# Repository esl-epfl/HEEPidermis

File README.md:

# Welcome!

HEEPidermis is a chip based on the open-source RISC-V platform [X-HEEP](https://github.com/esl-epfl/x-heep) intended to record Galvanic Skin Response (GSR) and Impedance (Z).
HEEPidermis is capable of injecting arbitrary-wave currents on the skin with an 8-bit iDAC and measure voltage through a 14-bit VCO-based ADC.
Parameters of the iDAC and ADC can be programmed dynamically using the on-board Ibex CPU. Acquired data can be stored in the 16 kB RAM memory for on-chip processing, compression, and transmission.

HEEPidermis can be interfaced through JTAG for code-debugging, SPI to obtain recordings from memory, or UART.
External ADCs and peripherals can also be commanded via SPI.

The Direct Memory Access (DMA) block allows the chip to operate autonomously without the constant interaction of the CPU. Given proper configuration, the DMA can take care of controlling the current injection profile, read data from the local ADC (or an external one), store data and/or transmit it through SPI.
The DMA can additionally re-direct data to a digital Level Crossing (dLC) block to filter data and reduce the output data rate. The output of the dLC can be stored in memory (along timestamps) or be exposed to be used as feedback loop for the analog front-end, interface with transmission circuits or as input to Spiking Neural Networks.
The dLC block also accepts inputs from analog LC ADCs (instead of the on-chip ADC).

HEEPidermis can also decimate 1-bit ΔΣ-ADCs' output with an integrated CIC filter or, alternatively, with an integrated custom smoothing stage, followed by the dLC block.

Being based on the X-HEEP platform, you can check its documentation on how to program, debug, or understand how it was built. We suggest using the [vendorized X-HEEP's documentation](../../hw/vendor/x-heep/docs/source/index.rst).
For all HEEPidermis-specific documentation, please refer to the documentation below.

<p align="center">

&nbsp;&nbsp;&nbsp;

</p>

## Index

- **Analog Front End**
  - [Analog subsystem](hw/ip/analog_subsystem/README.md)
  - [iDAC](hw/vendor/analog-library/iDAC/docs/README.md)
  - [VCO](hw/vendor/analog-library/VCO/docs/README.md)

- **Digital Back End**
  - [CPU](./docs/source/DBE/CPU.md)
  - [DMA (how we use it)](./docs/source/DBE/DMA.md)
  - [DMA](hw/vendor/x-heep/docs/source/Peripherals/DMA.md)
  - [SPI host](hw/vendor/x-heep/docs/source/Peripherals/SPI.md)
  - [SPI slave](hw/vendor/x-heep/docs/source/Peripherals/SPI_slave.md)
  - [digital Level-Crossing](hw/vendor/x-heep/docs/source/ExternalPeripherals/dLC.md)
  - [ΔΣ decimation (CIC filter)](./docs/source/DBE/CIC_filter.md)
  - [ΔΣ decimation (SES filter)](./docs/source/DBE/SES_filter.md)

- **PCBs**
  - [CHEEP-boards](./hw/vendor/cheep-boards/) - To program and provide power
  - [Breakout board](./hw/vendor/breakout-board/) - To solder the cheep and connect it to the CHEEP-boards.

- **Software**
  - [Desktop GUI](./sw/gui/README.md)

- **Related documents**
  - [HEEPidermis](https://arxiv.org/abs/2509.04528)
  - [ΔΣ Decimation theory](https://ieeexplore.ieee.org/abstract/document/11044062)
  - [iDAC precursor](https://ieeexplore.ieee.org/document/11044212)
  - [VCO Design](https://arxiv.org/abs/2509.06698)

## Desktop GUI

HEEPidermis includes a desktop GUI to configure the board, build firmware, record GSR signals, and visualize and analyze recordings. Adjust the injected current and sampling frequency live, explore saved recordings, and export your data to CSV.

Launch it from the repository root with:

```sh
make gui
```

See the [GUI documentation](./sw/gui/README.md) for installation requirements and usage instructions.

## Evaluating trade-offs in GSR recording

HEEPidermis is a complex SoC, and acquiring GSR keepeing a proper range, sensitivity, dynamic range, resolution and power can be very tricky! To aid in the process of choosing the right parameters we have modeled the performance and consumption of our front-end and integrated it into a visual model with which you can play.

You can use the plotter in two different ways:

1. **Forward control**: You choose the operating variables (injected current and sampling frequency) and study the obtained sensitivity for a given baseline value of conductivity (G)
2. **Target**: You select a target sensitivty and power consumption and let the tool find the optimal configuration.

To view the interactive plotter on your browser (forward mode only) run:
```
make plotter
```

## Making a GSR recording

We make GSR recordings by biasing the skin to the LDO's output at 0.8 V and using a second electrode to train current from the skin using the iDAC. The VCO measures that same node and the CPU computes the drop (knowing the LDO's output).

Because the computation is far from trivial we have added [a GSR SDK](./sw/external/lib/sdk/GSR) that takes care of managing peripherals and parameters to do the correct conversion to skin's conductance in nS. You can run the example application:

```
make app PROJECT=test_reconstruction BOOT_MODE=force
make verilator-run BOOT_MODE=force # Takes long, be patient :P (or cancel anytime with Ctrl+C and go ahead with the next step)
make verilator-waves
```

You will be able to see the input resistance (in Ω) and at the top (in yellow) the computed conductance (in nS). This simulation uses the behavioral models of the front-end, including an approximation of the VCO's measured phase noise.

## Prerequisites

Since this project is based on _X-HEEP_, it has the same prerequisites.

1. Follow _X-HEEP_'s [_Prerequisite_](https://github.com/esl-epfl/x-heep/tree/main#prerequisite) section to download the necessary tools.
To correctly generate hardware and software, an extended version of the _core-v-mini-mcu_ environment is required. To install it run:
   ```Bash
   make conda
   ```
Make sure the Conda environment is active:
   ```Bash
   conda activate heepidermis
   ```

2. Make sure that the following tools are available in your system's `PATH`:
   - To compile code: **RISC-V toolchain version 2022.01.17**, supporting at least `rv32imc`. Newer versions will work but compilation will have a bug when reporting memory usage.
   - To format SystemVerilog (in case you want to open a PR): **Verible version 0.0-4023-gc1271a00**
   - To simulate (open source): **Verilator 4.210**
   - To see waveforms out of Verilator: **GTKWave**
   - In case you have the licences:
     - Siemens QuestaSim version 2020.4 or above
     - Synopsys Design Compiler version 2020.09 or above

You can follow the instructions on how to install these tools on the [X-HEEP documentation - Manual setup](https://x-heep.readthedocs.io/en/latest/GettingStarted/Setup.html#manual-setup).

## Preparing the Boards

The easiest way to test HEEPidermis is to use the [CHEEP-boards](./hw/vendor/cheep-boards/), which provide all the tools (sw and hardware) to supply power and program HEEPidermis.

HEEPidermis is soldered (or placed on a socket) on the [breakout board](./hw/vendor/breakout-board/).

After soldering everything, you also need to:

### Connect chewing-gums

The chewing-gum (CG) boards are small shields that are connected to the main board, and which can be used to provide power or reference voltages to HEEPidermis, and measure that consumption.

| CG | Function | Nominal value | CG | Function | Nominal value |
| :--- | :--- | :--- | :--- | :--- | :--- |
| 6 | DCORE VDD | 0.8 V | 7 | ACORE VDD | 1.2 V |
| 5 | IO VDD | 1.8 V | 8 | iREF | Connect a source of 400 nA |
| 4 | not used | - | 9 | REF VDD | 1.2 V |
| 3 | not used | - | 10 | LDO VREF | 0.8 V |
| 2 | not used | - | 11 | VCO VDD | 0.8 V |
| 1 | not used | - | 12 | LDO VDD | 1.2 V |

> _Note that the bottom three CGs on the picture below are not used, they are just used to inject voltages here and there with an external cable for testing._

⚠️ Remember to solder a shunt resistor below the CG! ~10 Ω should do fine for the range 1-100 µW. Consider that the INA will amplify the drop by 1000-2000×, has an offset of some 10s µV, and it cannot output more than 3.3 V.

### Connect jumpers and switches

On the main board
* Each CG has three jumpers. To control them with the trimmer, connect the jumper next to it towards its screw. Connect the jumper on the side away from the trimmer to turn the power on. Connect the jumper innermost to the main baord away from the test point to make the output go to the main board.
* Connect the jumper for the IO VDD (next to CG 8) on 1.8 V
* No need to connect any jumper next to the oscilaltor (bottom of the main board)

On the breakout board there are several places where to connect jumpers to use the cheep on different configurations. Mainly, there are two rulers of pin headers around the cheep which can be used to connect or disconnect supplies. Many of them are short-circuited on both sides, so you just use the headers as test points or to inject a signal. The rest are marked with what would get to the cheep if you close the jumper. Additionally there are three-pin jumpers for you to choose what to supply the cheep with: an ideal supply coming from the main board's chewing gums, or a voltage/current coming from the on-cheep supplies.

Check the table on [the breakout board's readme](./hw/vendor/cheep-boards/) to see what connects what.

> ❗There are two pads on the bottom of the board that need to be short-circuited: They will connect the clock input to the cheep. You can select where to take the clock, if you have no clue what to do, put some solder tin on the two pair of pads that point to the main board to take the clock from there. Don't worry if you make a mistake and short a bit the other, it's not the end of the world.

There is a pair of switches on the breakout board, to the left of the cheep. You can eiter solder the switches to select the boot mode, or you can short with tin them the mid-pin with the one closest to the cheep to only use JTAG mode (explained below).

### Bug correction

🪲 You need to cut the pin below the `value` pin (the outter most pin, in row 31 of the main board) in the connector to the main board or nothing will work, sorry.

## Programming the ASIC

You can program the ASIC through 3 alternatives:
 - JTAG
 - Loading an external flash that HEEPidermis can read through SPI
 - Loading the program in RAM through the SPI slave peripheral

### Programming through JTAG

You need to connect the JTAG interface to an FTDI chip. This is avaialble on the [EPFL programmer](https://github.com/esl-epfl/x-heep-programmer-pmod) or on the [CHEEP boards](https://eslgit.epfl.ch/heep/cheep-boards) (currently only available upon request).

1. The BOOT switches should be set to

| Signal     | Value |
|------------|-------|
| FLASH_EXEC | 0     |
| BOOT_SEL   | 0     |

2. Set the system clock to 1 MHz. You can do that in two steps if you have the CHEEP board, and have exported the variable `$CHEEP_BOARDS` pointing to the folder where the repo is.
```bash
make board_config
make board_freq PLL_FREQ=1_000_000  #default
```

3. Build the SW/HW stack of the cheep
```bash
make cheep-gen
```

4. Compile the code
```bash
make app BOOT_MODE=jtag
```

1. Open openOCD and picocom to see the UART output
```bash
make jtag_open
```
1. Open GDB and run the program
```bash
make jtag_run
```
Useful commands:
> `c` (continue)
>
> `monitor reset hart`
>
> `monitor pc _start`
>
> `si` (next instruction)
>
> `disassembler`
>
> `x/8i` (see the following instructions).

1. Exit GDB with `ctrl+C` and type `quit`
2. Close the openOCD and uart terminals with
```bash
make jtag_close
```

### Programming from the FLASH

Testing... we seem to have a bug on the main board that prevents this from working 😬

### Programming through SPI

Testing...

## RTL Simulation

The included [`makefile`](./makefile) proves all the necessary rules to build _HEEPidermis_:

1. Generate all the RTL files (and software headers):
   ```bash
   make cheep-gen
   ```
   Some _X-HEEP_ configuration parameters (e.g. `BUS`, `MEMORY_BANKS` etc.) are still supported, although the default configuration may differ (check [`peripherals_config`](./config/peripherals_config)). In general, these should not be passed through the makefile targets but should be configured in the hjson files in the `config` folder.

2. Build the simulation model:
   ```bash
   make verilator-build     # Verilator
   make questasim-build     # QuestaSim
   ```

3. The software build process is primarily handled by _X-HEEP_, and most of its [example applications](./hw/vendor/x-heep/sw/applications/) will work on _HEEPidermis_ as well. You can choose other `BOOT_MODE`, just be sure to match it with the one used with `make *-build` (by default they use `fore`). `force` will be the faster for simulation.

```bash
make app PROJECT=test_dlc_vco BOOT_MODE=force
```

The combinations of compatible linker and boot modes can be found here:

1. Launch the simulation with the compiled firmware:
   ```bash
   make verilator-run       # Verilator with waveforms dump
   make verilator-opt       # Verilator without waveforms dump
   make questasim-run       # QuestaSim
   make questasim-gui       # QuestaSim with GUI
   ```

   You can also set other parameters like the `FUSESOC_FLAGS`, `LOG_LEVEL`, `BOOT_MODE`, `VCD_MODE`, etc. to customize the simulation. Refer to the [`makefile`](./makefile) for more details.

2. _HEEPidermis_ `stdout` is exposed through a UART DPI interface at `/dev/pts/<N>`, where `N` is a number printed on the simulation log during execution. You can connect to it using `screen` or similar tools, e.g.:
   ```bash
   screen /dev/pts/0
   ```
   The UART output is also stored to the `uart.log` file in the common simulation directory (`build/sim-common/uart.log`).
   > Using `printf()` will significantly increase the firmware execution time and therefore the simulation. For quick debugging, it recommended to use the return value from `main` instead. When it is _not_ zero, the testbench will print it out at the end of the simulation.

3. The waveforms dumped during the simulation can be opened using:
   ```bash
   make verilator-waves # after Verilator simulation
   make questasim-waves # after QuestaSim simulation
   ```

This will open the waveforms (example from `test_dlc_vco` application):

Assuming that your firmware is already available, steps 1., 3., and 4. can be repeated with a single command using the `verilator-sim` or `questasim-sim` targets.

# Questions?

Have questions? curiosities? ideas on how to exploit HEEPidermis? Want to contribute on following versions of the SoC?
Drop an email :) juan.sapriza@epfl.ch

# 📄 Reference

Want to know more details? Found HEEPidermis useful for your research? Cite our [LASCAS paper](https://ieeexplore.ieee.org/document/11457136).

```
@INPROCEEDINGS{11457136,
  author={Sapriza, Juan and Grassano, Beatrice and Naclerio, Alessio and Quadri, Filippo and Terzano, Tommaso and Mallasén, David and Schiavone, Davide and Leplae, Robin and Moullet, Jérémie and Levisse, Alexandre and Müller, Christoph and Graziano, Mariagrazia and Miguez, Matías and Atienza, David},
  booktitle={2026 IEEE 17th Latin America Symposium on Circuits and System (LASCAS)},
  title={HEEPidermis: A Versatile SoC for BioZ Recording},
  year={2026},
  pages={1-5},
  doi={10.1109/LASCAS67804.2026.11457136}}
```

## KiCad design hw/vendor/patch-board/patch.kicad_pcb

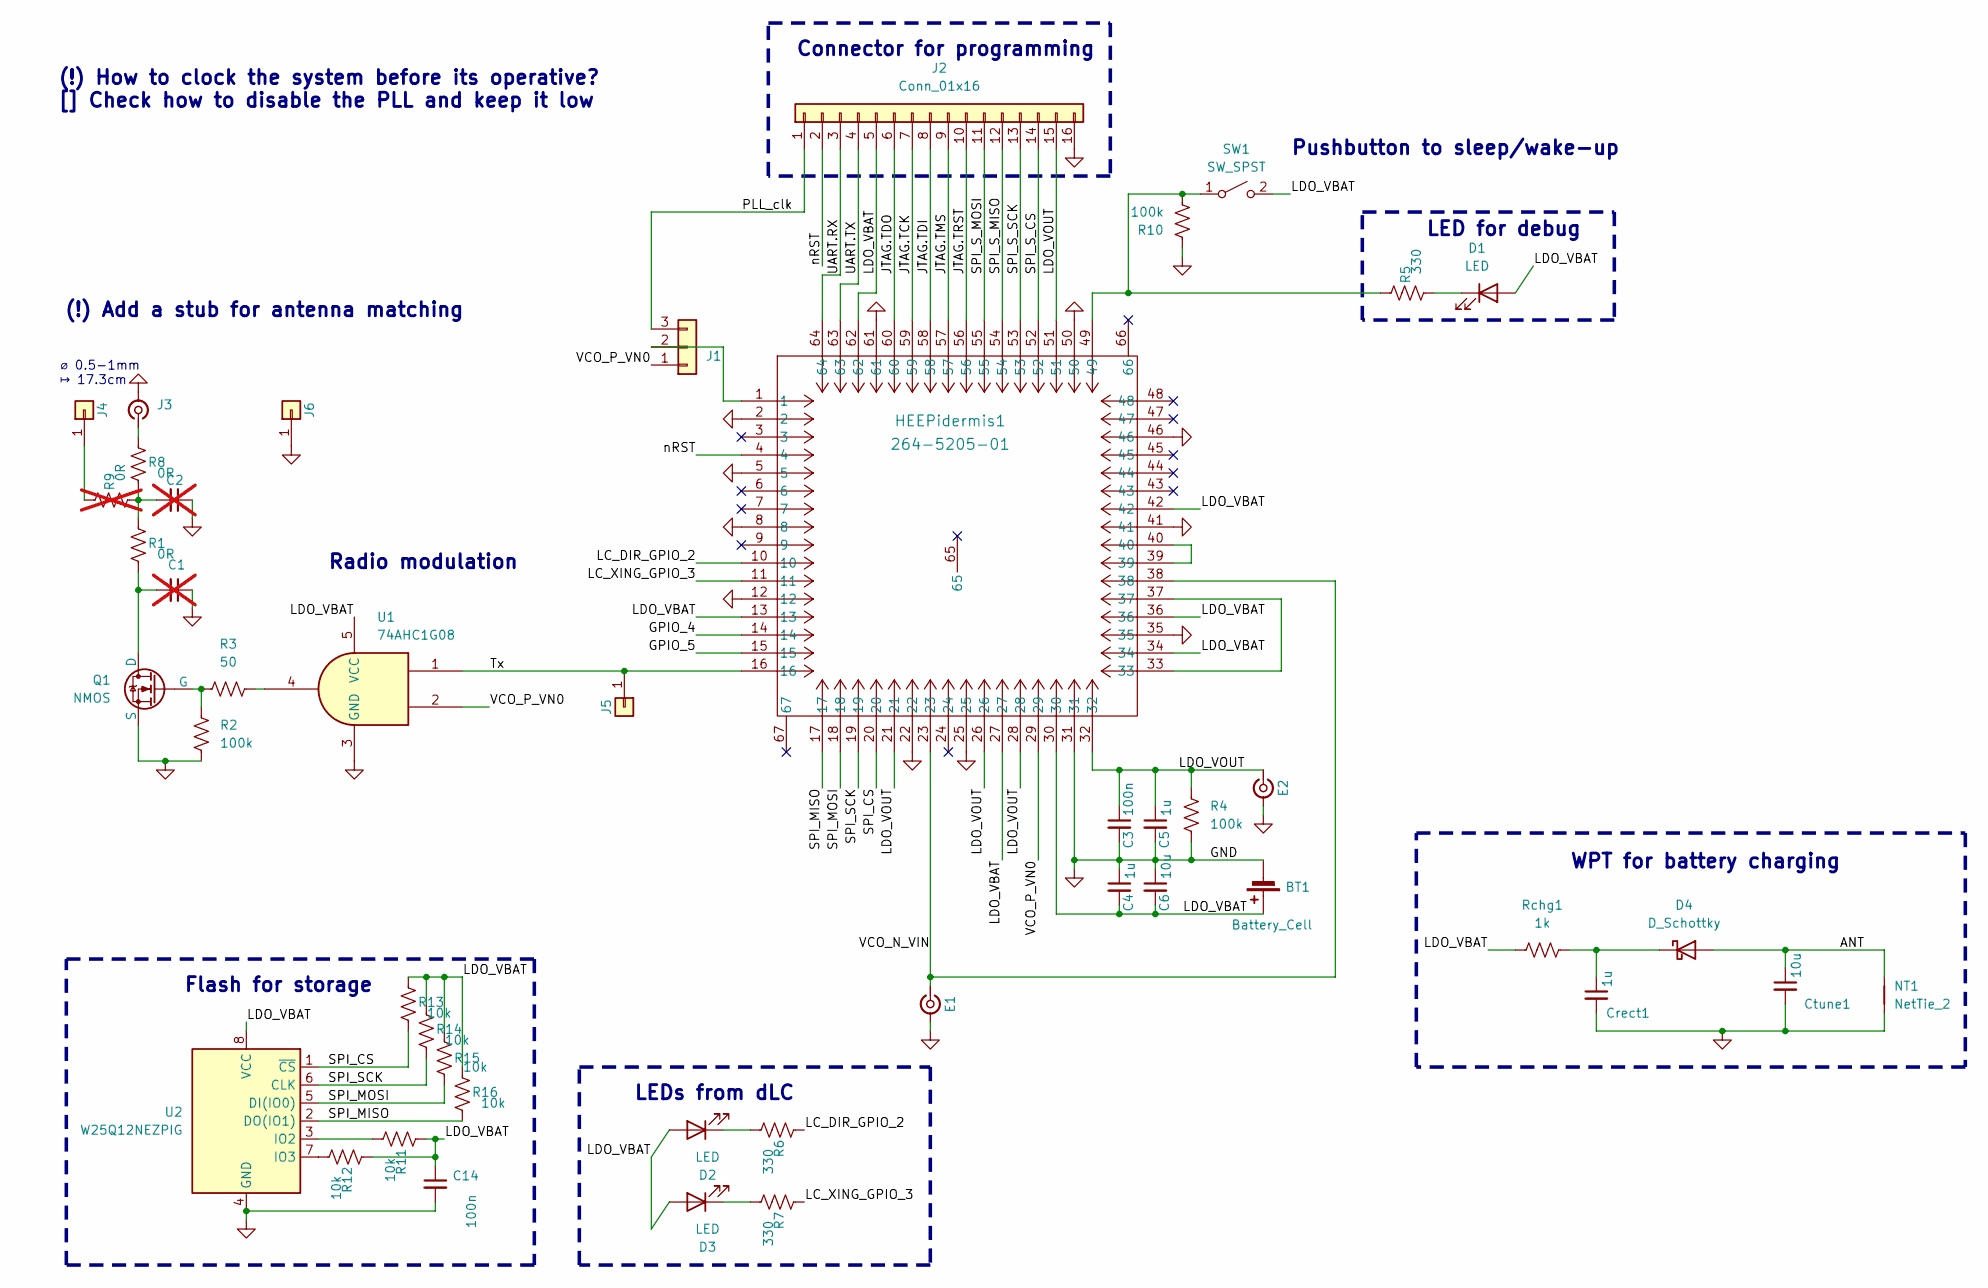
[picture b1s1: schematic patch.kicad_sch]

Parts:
BT1: Battery_Cell; BatteryHolder_Seiko_MS621F
C1, C2: C_0603_1608Metric; Mouser Part Number 80-C0805C104Z3V; Digikey Part Number 399-9158-1-ND; not fitted
C3, C14: 100n; C_0603_1608Metric; Mouser Part Number 80-C0805C104Z3V; Digikey Part Number 399-9158-1-ND
C4, C5: 1u; C_0603_1608Metric; Mouser Part Number 80-C0805C104Z3V; Digikey Part Number 399-9158-1-ND
C6: 10u; C_0603_1608Metric; Mouser Part Number 80-C0805C104Z3V; Digikey Part Number 399-9158-1-ND
Crect1: 1u; C_0603_1608Metric; Mouser Part Number 80-C0805C104Z3V; Digikey Part Number 399-9158-1-ND
Ctune1: 10u; C_0603_1608Metric; Mouser Part Number 80-C0805C104Z3V; Digikey Part Number 399-9158-1-ND
D1, D2, D3: LED; LED_0603_1608Metric
D4: D_Schottky; D_0603_1608Metric
E1, E2: Conn_Coaxial_Small; 4mm_snap_socket
HEEPidermis1: 264-5205-01; QFN-64-1EP_9x9mm_P0.5mm_EP3.4x3.4mm
J1: Conn_01x03; PinHeader_1x03_P1.00mm_Horizontal
J2: Conn_01x16; PinHeader_1x16_P1.00mm_Horizontal
J3: Conn_Coaxial_Small
J4, J5, J6: Conn_01x01; PinHeader_1x01_P2.54mm_Vertical
NT1: NetTie_2; 1MHz_coil_29x14
Q1: NMOS; SOT-323_SC-70_Handsoldering
R1, R8: 0R; R_0603_1608Metric
R2, R4, R10: 100k; R_0603_1608Metric
R3: 50; R_0603_1608Metric
R5, R6, R7: 330; R_0603_1608Metric
R9: 0R; R_0603_1608Metric; not fitted
R11, R12, R13, R14, R15, R16: 10k; R_0603_1608Metric
Rchg1: 1k; R_0603_1608Metric
SW1: SW_SPST; SPST_1.6x3mm
U1: 74AHC1G08; SOT-353_SC-70-5_Handsoldering
U2: W25Q12NEZPIG; SOIC-8_5.23x5.23mm_P1.27mm

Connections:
/ANT: Ctune1.1, D4.2 (A), NT1.2
/GPIO_4: HEEPidermis1.14
/GPIO_5: HEEPidermis1.15
/JTAG.TCK: HEEPidermis1.59, J2.7
/JTAG.TDI: HEEPidermis1.58, J2.8
/JTAG.TDO: HEEPidermis1.60, J2.6
/JTAG.TMS: HEEPidermis1.57, J2.9
/JTAG.TRST: HEEPidermis1.56, J2.10
/LC_DIR_GPIO_2: HEEPidermis1.10, R6.2
/LC_XING_GPIO_3: HEEPidermis1.11, R7.2
/LDO_VBAT: BT1.1 (+), C4.2, C6.2, C14.1, D1.2 (A), D2.2 (A), D3.2 (A), HEEPidermis1.13, HEEPidermis1.27, HEEPidermis1.30, HEEPidermis1.34, HEEPidermis1.36, HEEPidermis1.42, HEEPidermis1.62, J2.5, R11.2, R12.2, R13.2, R14.2, R15.2, R16.2, Rchg1.1, SW1.2 (B), U1.5 (VCC), U2.8 (VCC)
/LDO_VOUT: C3.1, C5.1, E2.1 (In_1), HEEPidermis1.21, HEEPidermis1.26, HEEPidermis1.28, HEEPidermis1.32, HEEPidermis1.51, J2.15, R4.1
/PLL_clk: J1.3, J2.1
/SPI_CS: HEEPidermis1.20, R13.1, U2.1 (~CS)
/SPI_MISO: HEEPidermis1.17, R16.1, U2.2 (DO(IO1))
/SPI_MOSI: HEEPidermis1.18, R15.1, U2.5 (DI(IO0))
/SPI_SCK: HEEPidermis1.19, R14.1, U2.6 (CLK)
/SPI_S_CS: HEEPidermis1.52, J2.14
/SPI_S_MISO: HEEPidermis1.54, J2.12
/SPI_S_MOSI: HEEPidermis1.55, J2.11
/SPI_S_SCK: HEEPidermis1.53, J2.13
/Tx: HEEPidermis1.16, J5.1 (Pin_1_1), U1.1
/UART.RX: HEEPidermis1.64, J2.3
/UART.TX: HEEPidermis1.63, J2.4
/VCO_N_VIN: E1.1 (In_1), HEEPidermis1.23, HEEPidermis1.38
/VCO_P_VN0: HEEPidermis1.29, J1.1, U1.2
/nRST: HEEPidermis1.4, J2.2
GND: BT1.2 (-), C1.1, C2.1, C3.2, C4.1, C5.2, C6.1, C14.2, Crect1.2, Ctune1.2, E1.2 (Ext), E2.2 (Ext), HEEPidermis1.2, HEEPidermis1.5, HEEPidermis1.8, HEEPidermis1.12, HEEPidermis1.22, HEEPidermis1.25, HEEPidermis1.31, HEEPidermis1.35, HEEPidermis1.41, HEEPidermis1.46, HEEPidermis1.50, HEEPidermis1.61, J2.16, J3.2 (Ext), J6.1 (Pin_1_1), NT1.1, Q1.3 (S), R2.1, R4.2, R10.2, U1.3 (GND), U2.4 (GND)
unnamed: C2.2, R1.2, R8.1, R9.1
unnamed: D1.1 (K), R5.1
unnamed: D2.1 (K), R6.1
unnamed: D3.1 (K), R7.1
unnamed: Crect1.1, D4.1 (K), Rchg1.2
unnamed: HEEPidermis1.33, HEEPidermis1.37
unnamed: HEEPidermis1.39, HEEPidermis1.40
unnamed: HEEPidermis1.1, J1.2
unnamed: J3.1 (In), R8.2
unnamed: J4.1 (Pin_1_1), R9.2
unnamed: C1.2, Q1.1 (D), R1.1
unnamed: Q1.2 (G), R2.2, R3.1
unnamed: R3.2, U1.4
unnamed: HEEPidermis1.49, R5.2, R10.1, SW1.1 (A)
unnamed: R11.1, U2.3 (IO2)
unnamed: R12.1, U2.7 (IO3)

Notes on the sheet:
LED for debug
(!) Add a stub for antenna matching
LEDs from dLC
WPT for battery charging
⌀ 0.5-1mm ↦ 17.3cm
Flash for storage
(!) How to clock the system before its operative? [] Check how to disable the PLL and keep it low
Connector for programming
Pushbutton to sleep/wake-up
Radio modulation

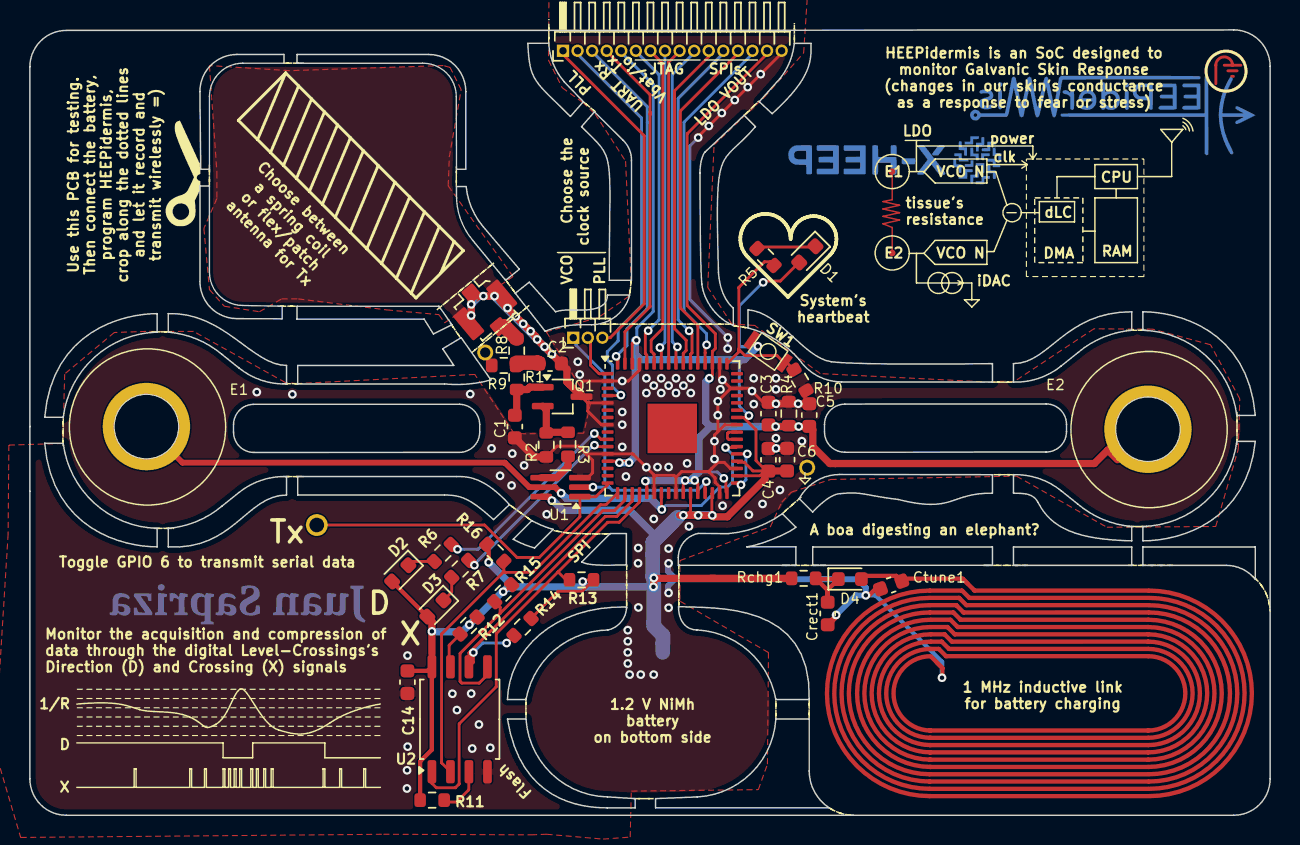
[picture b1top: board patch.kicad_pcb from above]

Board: 2 copper layers, 85.1 x 53.9 mm, 45 parts (1 on the bottom side), 42 nets.

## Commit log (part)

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2025-09-09 initial clean commit
2026-01-12 First attempt to use scanf. I think there is a short on HW of the main pcb
2026-04-03 Experiments with DSM
2026-04-04 Obtained plots for paper
2026-04-06 Added more plots for the SES paper
2026-04-06 Added test with dLC
2026-04-08 Tests on the dLC
2026-04-08 Updated makefile to force to update the environment and added required packages
2026-04-08 added scipy as requirement
2026-04-08 Added some hype into the readme
2026-04-13 Testing different transfers for the SES
2026-04-13 Adjusted dLC params to discard 1 bit and not take large changes as negative
2026-04-13 Added better extraction from dLC + better reconstruction
2026-04-15 Added patch to expose the last word of the tc_ram bank
2026-04-15 Added test app
2026-04-15 Accelerated UART to almost maximum
2026-04-20 Tuned plots
2026-04-22 updated plots
2026-04-22 Ported the VCO's behavioral into a polynomial and added some random noise +- 100 Hz
2026-04-22 ⚠️ MADE ALL test_GSR 100x FASTER WRT REAL TIME (resistor, vco gain and sampling frequency)
2026-04-23 Corrected transfer
2026-04-28 Comparison
2026-05-01 Added power measurement plots
2026-05-05 Added mention on the README
2026-05-05 Added Blanca's authorship
2026-05-12 Measured more CIC/SES power consumptions
2026-05-26 Added fusesoc and edalize to requirements
2026-05-26 Fixed event based application, and added reconstruction path
2026-05-27 ⚖ Automatic range adjustment (#10)
2026-06-04 characterized impact of N on digital power consumption (this commit + N-2 commit)
2026-06-04 resolution computation done and works with DMA
2026-06-04 added digital power consumption to plotter
2026-06-04 clean DMA main application
2026-06-04 playing around with dlc
2026-06-04 added read_batch for dma
2026-06-04 updated plotter to include all tradeoff plots (new analysis tabs)
2026-06-04 dma implemented in GSR_controller ! :)
2026-06-04 removed averaging idea
2026-06-04 refactored main application
2026-06-04 DMA works but no dlc (don't have the latest version). - Started reading in windows
2026-06-04 minor changes on plotter
2026-06-04 skip the first sample after init or config change
2026-06-04 moved files to evalute forlder and updated gitignore + minimal update to .gtkw
2026-06-04 finalize PR for range adjustement (no duty cycling yet)
2026-06-04 minor updated to plotter
2026-06-04 updated read_sample to read
2026-06-05 DMA handles duty cycling (PR done)
2026-06-05 adds the new FEA and comparison workflow.
